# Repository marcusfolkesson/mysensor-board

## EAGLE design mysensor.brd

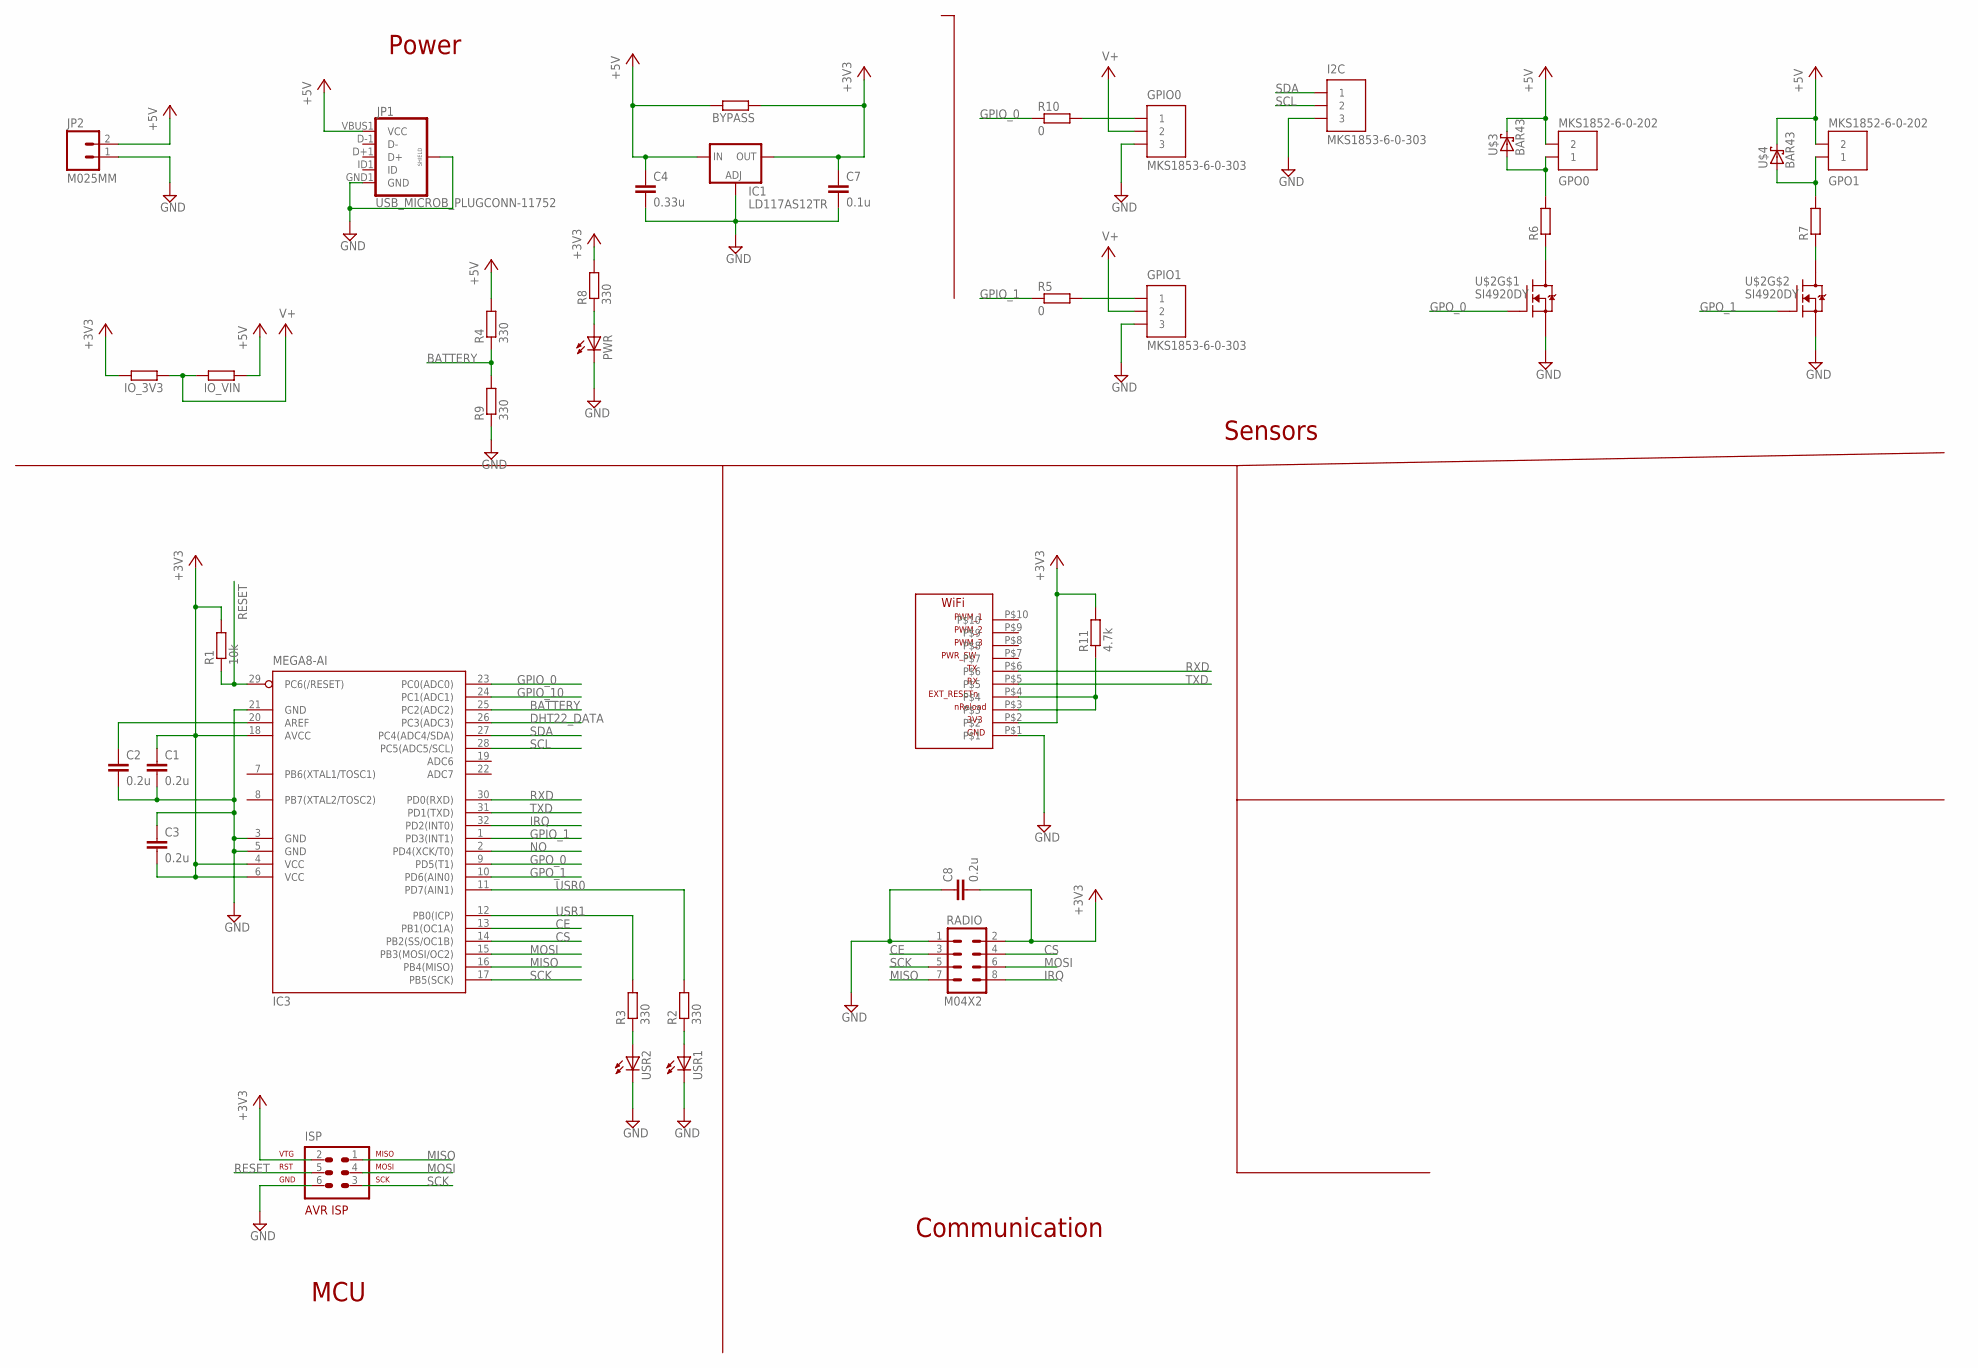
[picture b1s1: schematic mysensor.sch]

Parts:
BYPASS: R-EU_M0805; M0805
C1, C2, C3, C8: 0.2u; C0805
C4: 0.33u; C0805
C7: 0.1u; C0805
GPIO0, GPIO1: MKS1853-6-0-303
GPO0, GPO1: MKS1852-6-0-202
I2C: MKS1853-6-0-303
IC1: LD117AS12TR; SOT223
IC3: MEGA8-AI; TQFP32-08
IO_3V3: R-EU_M0805; M0805
IO_VIN: R-EU_M0805; M0805
ISP: AVR-ISP-6
JP1: USB_MICROB_PLUGCONN-11752; USB-B-MICRO-SMD_V03
JP2: M025MM; SCREWTERMINAL-5MM-2
PWR: LEDCHIP-LED0805; CHIP-LED0805
R1: 10k; R0805
R2, R3, R4, R8, R9: 330; M0805
R5, R10: 0; R0805
R6, R7: R-EU_M0805; M0805
R11: 4.7k; M0805
RADIO: M04X2; 2X4
U$1: WIFI232; WLAN
U$2: SI4920DY; SO-8
U$3, U$4: BAR43; SOT23
USR1, USR2: LEDCHIP-LED0805; CHIP-LED0805

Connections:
+3V3: BYPASS.1, C1.1, C3.2, C7.1, C8.2, IC1.4 (OUT), IC3.4 (VCC), IC3.6 (VCC), IC3.18 (AVCC), IO_3V3.2, ISP.2, R1.2, R8.2, R11.2, RADIO.2, U$1.P$2
+5V: BYPASS.2, C4.1, GPO0.2, GPO1.2, IC1.3 (IN), IO_VIN.1, JP1.VBUS1 (VCC), JP2.2, R4.2, U$3.3 (C), U$4.3 (C)
BATTERY: IC3.25 (PC2(ADC2)), R4.1, R9.2
CE: IC3.13 (PB1(OC1A)), RADIO.3
CS: IC3.14 (PB2(SS/OC1B)), RADIO.4
DHT22_DATA: IC3.26 (PC3(ADC3))
GND: C1.2, C2.2, C3.1, C4.2, C7.2, C8.1, GPIO0.3, GPIO1.3, I2C.3, IC1.1 (ADJ), IC3.3 (GND), IC3.5 (GND), IC3.21 (GND), ISP.6, JP1.GND1 (GND), JP1.SHIELD1 (SHIELD), JP1.SHIELD2 (SHIELD), JP1.SHIELD3 (SHIELD), JP2.1, PWR.C, R9.1, RADIO.1, U$1.P$1, U$2.1 (S), U$2.3 (S), USR1.C, USR2.C
GPIO_0: IC3.23 (PC0(ADC0)), R10.1
GPIO_1: IC3.1 (PD3(INT1)), R5.1
GPIO_10: IC3.24 (PC1(ADC1))
GPO_0: IC3.9 (PD5(T1)), U$2.2 (G)
GPO_1: IC3.10 (PD6(AIN0)), U$2.4 (G)
IRQ: IC3.32 (PD2(INT0)), RADIO.8
MISO: IC3.16 (PB4(MISO)), ISP.1, RADIO.7
MOSI: IC3.15 (PB3(MOSI/OC2)), ISP.4, RADIO.6
unnamed: R6.1, U$2.7 (D1)
unnamed: PWR.A, R8.1
unnamed: R2.1, USR1.A
unnamed: R3.1, USR2.A
unnamed: GPO0.1, R6.2, U$3.1 (A)
unnamed: GPIO1.1, R5.2
unnamed: R11.1, U$1.P$3, U$1.P$4
unnamed: GPIO0.1, R10.2
unnamed: R7.1, U$2.5 (D1)
unnamed: GPO1.1, R7.2, U$4.1 (A)
unnamed: C2.1, IC3.20 (AREF)
NO: IC3.2 (PD4(XCK/T0))
RESET: IC3.29 (PC6(/RESET)), ISP.5, R1.1
RXD: IC3.30 (PD0(RXD)), U$1.P$6
SCK: IC3.17 (PB5(SCK)), ISP.3, RADIO.5
SCL: I2C.2, IC3.28 (PC5(ADC5/SCL))
SDA: I2C.1, IC3.27 (PC4(ADC4/SDA))
TXD: IC3.31 (PD1(TXD)), U$1.P$5
USR0: IC3.11 (PD7(AIN1)), R2.2
USR1: IC3.12 (PB0(ICP)), R3.2
V+: GPIO0.2, GPIO1.2, IO_3V3.1, IO_VIN.2

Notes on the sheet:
Power
Sensors
MCU
Communication

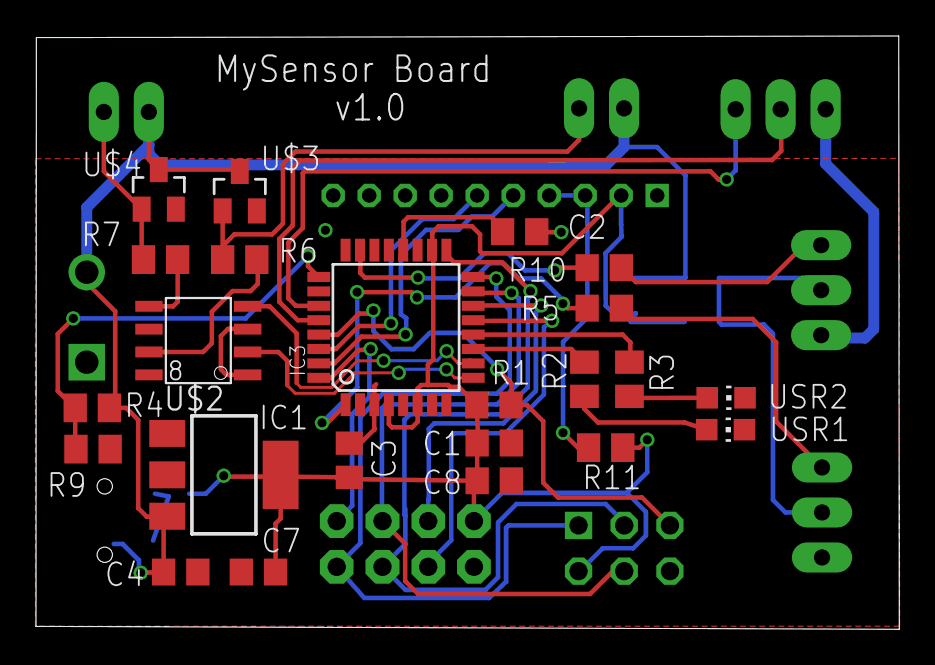
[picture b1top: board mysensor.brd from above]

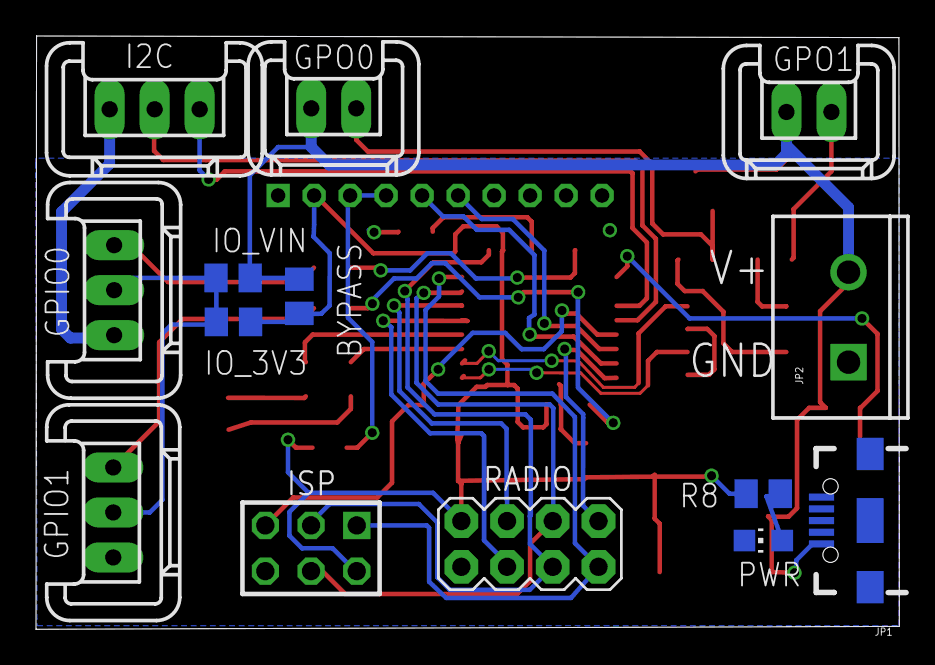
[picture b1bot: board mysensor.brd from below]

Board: 2 copper layers, 48.0 x 33.0 mm, 38 parts (14 on the bottom side), 33 nets.

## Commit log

2016-02-14 Updates for rev 1.0
    * Moved LDO to left, too close to pin header
    * Moved USR1/2 to right for not covered by wifi module
    * Removed ground plane under pcb antenna
    * Moved GPIO_1 to INT1
    * Possible to read battery power by ADC
    * Add V+ and GND text to skruvplint
2016-06-11 Unknown changes

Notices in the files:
parts and their libraries:
SparkFun-Connectors: Licensing: Creative Commons ShareAlike 4.0 International - https://creativecommons.org/licenses/by-sa/4.0
